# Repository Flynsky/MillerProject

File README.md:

This design is a TOP SECRET Miller Project.

Arbeits Aufteilung:
-  Ibex-Port (Handl)
- PCB, Schematic + Layout (Gewiese)
- USB PHY, ISO7816 Interface / Card VCC-Switching, Power Domains (Belm)
- Pin Assignment, Constraints, Bringup-Testinfrastruktur - Bindeglied zwischen Hardware und HDL (Drüen)

ToDo Redesign:
- USB-Phy reindesignen (voraussichtlich TUSB1106)
- zusätzlicher USB-Connector für Device-Mode-USB und Routing zum
TUSB1106. Also Referenzimplementierung kann hier das Sonata-Board
(lowRISC) dienen
- ISO7816-Interface: Das sind nur FPGA-Pins die an PIN-Header geroutet
werden. Ggf. noch Level-Shifter
- Alles raus was wir nicht brauchen
- Bissl hübscher machen

References
- [colone chips gatemate](https://colognechip.com/programmable-logic/gatemate/)
- [reference board GateMateA1-EVB](https://github.com/OLIMEX/GateMateA1-EVB)

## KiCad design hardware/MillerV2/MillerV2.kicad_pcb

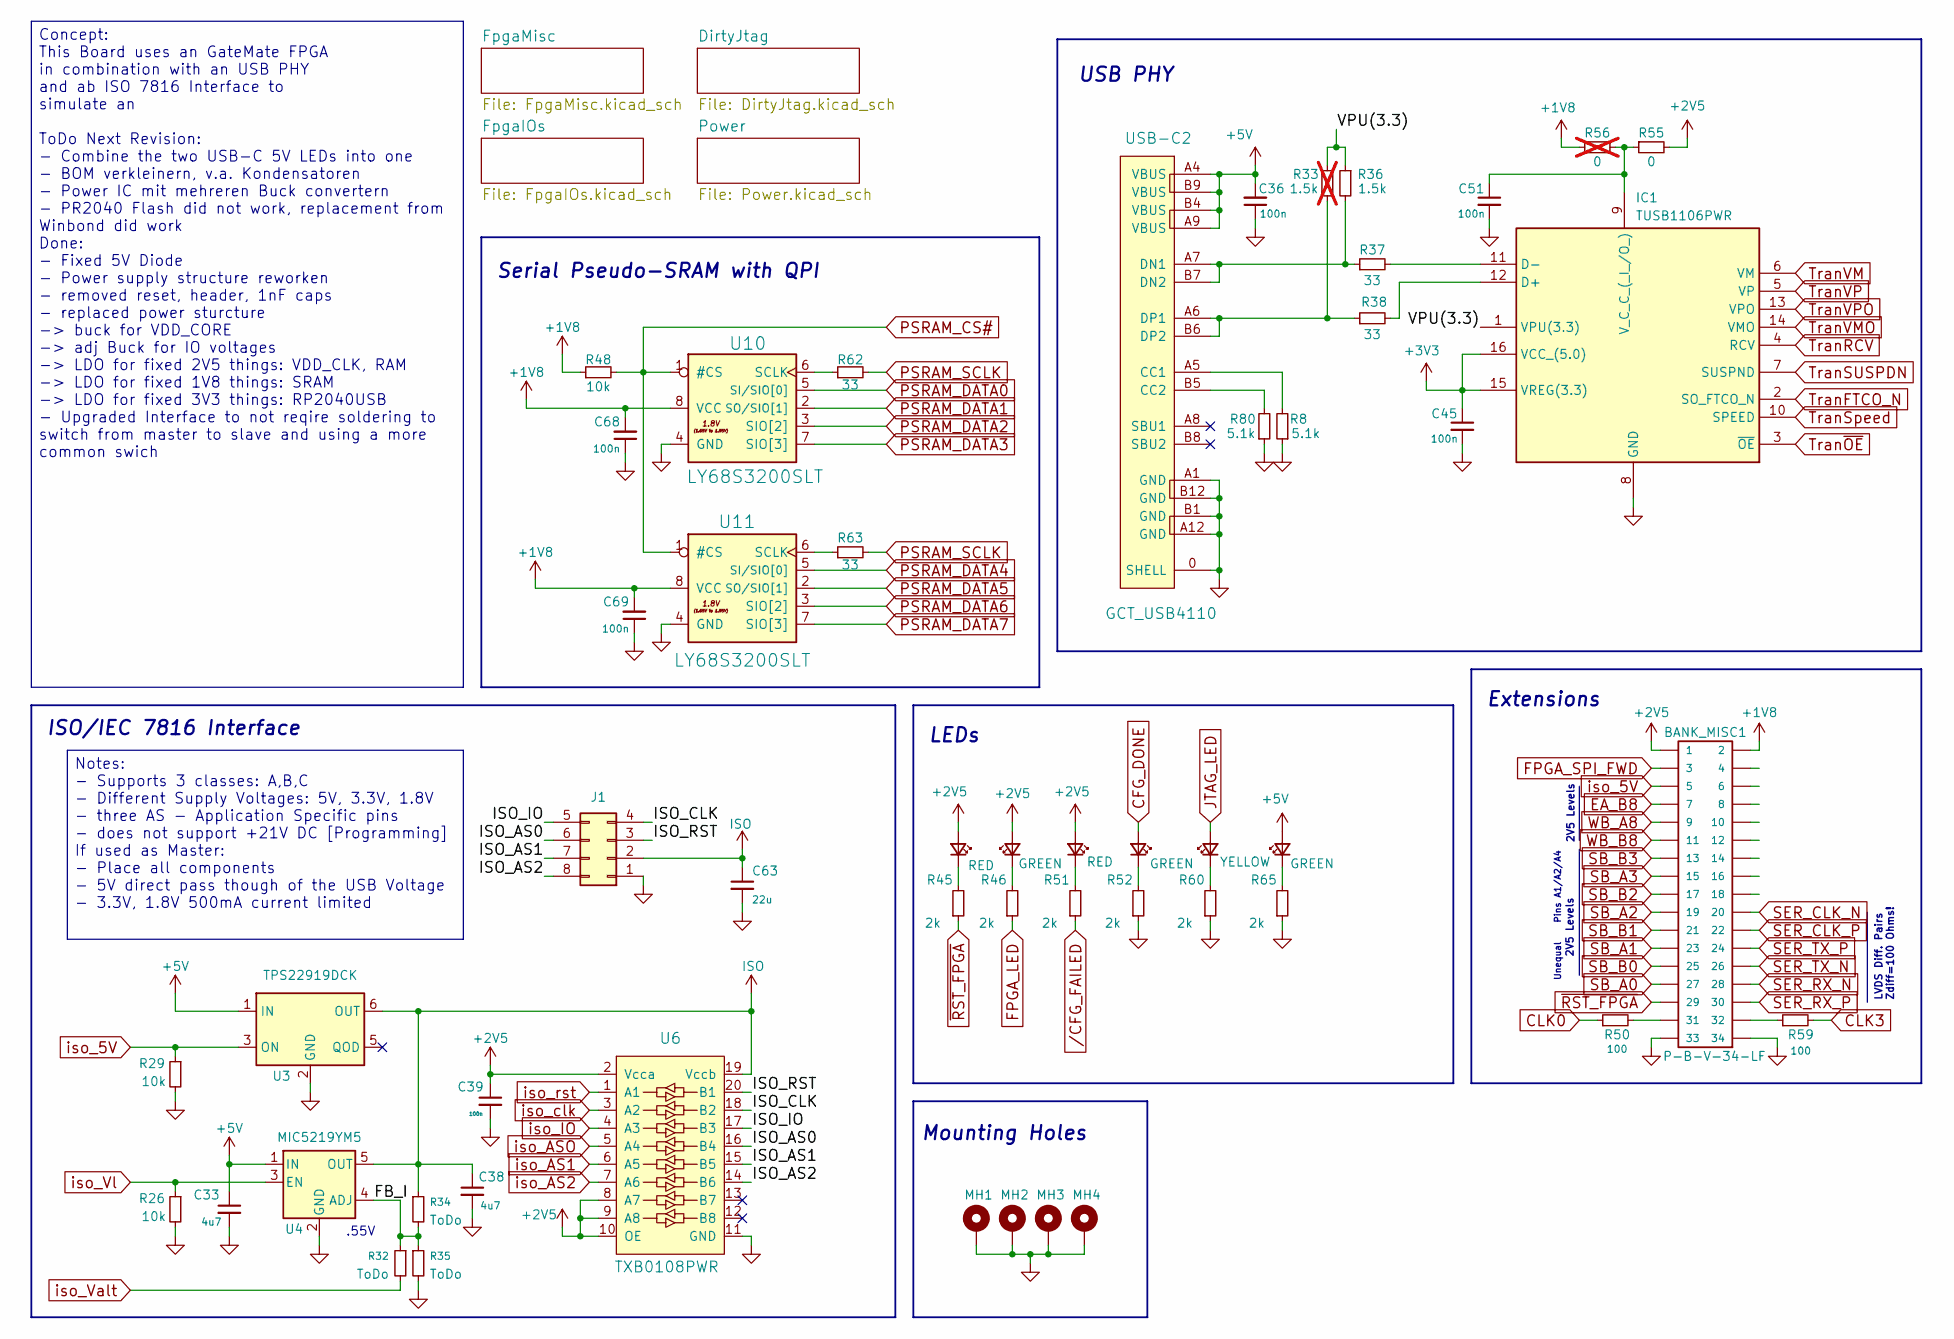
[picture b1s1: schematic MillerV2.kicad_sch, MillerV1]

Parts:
BANK_MISC1: P-B-V-34-LF; PinSocket_2x17_P2.54mm_Vertical_SMD
C33, C38: 4u7; C_0402_1005Metric
C36, C39, C45, C51, C68, C69: 100n; C_0402_1005Metric
C63: 22u; C_0805_2012Metric
CFG_DONE1: GREEN; LED_0402_1005Metric
CFG_FAIL1: RED; LED_0402_1005Metric
FPGA_LED1: GREEN; LED_0402_1005Metric
FPGA_RST2: RED; LED_0402_1005Metric
IC1: TUSB1106PWR; SOP65P640X120-16N; Mouser Part Number 595-TUSB1106PWR
J1: Conn_02x04_Counter_Clockwise; PinHeader_2x04_P2.54mm_Horizontal
JTAG_LED1: YELLOW; LED_0402_1005Metric
MH1, MH2, MH3, MH4: MountingHole_Pad; MountingHole_3.2mm_M3_Pad_Via
PWR_LED1: GREEN; LED_0402_1005Metric
R8, R80: 5.1k; R_0402_1005Metric
R26, R29, R48: 10k; R_0402_1005Metric
R32, R34, R35: ToDo; R_0402_1005Metric
R33: 1.5k; R_0402_1005Metric; not fitted
R36: 1.5k; R_0402_1005Metric
R37, R38, R62, R63: 33; R_0402_1005Metric
R45, R46, R51, R52, R60, R65: 2k; R_0402_1005Metric
R50, R59: 100; R_0402_1005Metric
R55: 0; R_0402_1005Metric
R56: 0; R_0402_1005Metric; not fitted
U3: TPS22919DCK; SOT-363_SC-70-6
U4: MIC5219YM5; SOT-23-5
U6: TXB0108PWR; TSSOP20_Pitch-0.65mm_6.6x4.5x1.2mm
U10, U11: LY68S3200SLT; SOIC-8_3.9x4.9mm_P1.27mm
USB-C2: GCT_USB4110; USB421603A

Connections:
+1V8: BANK_MISC1.2, C68.2, C69.2, R48.1, R56.1, U10.8 (VCC), U11.8 (VCC); also elsewhere on the board
+2V5: BANK_MISC1.1, C39.1, CFG_FAIL1.2 (A), FPGA_LED1.2 (A), FPGA_RST2.2 (A), R55.2, U6.2 (Vcca), U6.8 (A7), U6.9 (A8), U6.10 (OE); also elsewhere on the board
+3V3: C45.1, IC1.15 (VREG(3.3)), IC1.16 (VCC_(5.0)); also elsewhere on the board
+5V: C33.1, C36.2, PWR_LED1.2 (A), U3.1 (IN), U4.1 (IN), USB-C2.A4 (VBUS), USB-C2.A9 (VBUS), USB-C2.B4 (VBUS), USB-C2.B9 (VBUS); also elsewhere on the board
/FB_I: R32.1, R34.2, R35.1, U4.4 (ADJ)
/ISO_AS0: J1.6, U6.16 (B4)
/ISO_AS1: J1.7, U6.15 (B5)
/ISO_AS2: J1.8, U6.14 (B6)
/ISO_CLK: J1.4, U6.18 (B2)
/ISO_IO: J1.5, U6.17 (B3)
/ISO_RST: J1.3, U6.20 (B1)
/VPU(3.3): IC1.1 (VPU(3.3)), R33.1, R36.1
CFG_DONE: CFG_DONE1.2 (A); also elsewhere on the board
CLK0: R50.1; also elsewhere on the board
CLK3: R59.2; also elsewhere on the board
EA_B8: BANK_MISC1.7; also elsewhere on the board
FPGA_LED: R46.1; also elsewhere on the board
FPGA_SPI_FWD: BANK_MISC1.3; also elsewhere on the board
GND: BANK_MISC1.33, BANK_MISC1.34, C33.2, C36.1, C38.2, C39.2, C45.2, C51.2, C63.2, C68.1, C69.1, IC1.8 (GND), J1.1, MH1.1 (1_1), MH2.1 (1_1), MH3.1 (1_1), MH4.1 (1_1), R8.1, R26.2, R29.2, R35.2, R52.1, R60.1, R65.1, R80.1, U3.2 (GND), U4.2 (GND), U6.11 (GND), U10.4 (GND), U11.4 (GND), USB-C2.0 (SHELL), USB-C2.A1 (GND), USB-C2.A12 (GND), USB-C2.B1 (GND), USB-C2.B12 (GND); also elsewhere on the board
ISO: C38.1, C63.1, J1.2, R34.1, U3.6 (OUT), U4.5 (OUT), U6.19 (Vccb)
JTAG_LED: JTAG_LED1.2 (A); also elsewhere on the board
unnamed: BANK_MISC1.31, R50.2
unnamed: BANK_MISC1.32, R59.1
unnamed: CFG_DONE1.1 (K), R52.2
unnamed: CFG_FAIL1.1 (K), R51.2
unnamed: FPGA_LED1.1 (K), R46.2
unnamed: FPGA_RST2.1 (K), R45.2
unnamed: IC1.12 (D+), R38.2
unnamed: IC1.11 (D-), R37.2
unnamed: C51.1, IC1.9 (V_C_C_(_I_/O_)), R55.1, R56.2
unnamed: JTAG_LED1.1 (K), R60.2
unnamed: PWR_LED1.1 (K), R65.2
unnamed: R62.1, U10.6 (SCLK)
unnamed: R63.1, U11.6 (SCLK)
unnamed: R8.2, USB-C2.A5 (CC1)
unnamed: R80.2, USB-C2.B5 (CC2)
unnamed: R36.2, R37.1, USB-C2.A7 (DN1), USB-C2.B7 (DN2)
unnamed: R33.2, R38.1, USB-C2.A6 (DP1), USB-C2.B6 (DP2)
PSRAM_CS#: R48.2, U10.1 (#CS), U11.1 (#CS); also elsewhere on the board
PSRAM_DATA0: U10.5 (SI/SIO[0]); also elsewhere on the board
PSRAM_DATA1: U10.2 (SO/SIO[1]); also elsewhere on the board
PSRAM_DATA2: U10.3 (SIO[2]); also elsewhere on the board
PSRAM_DATA3: U10.7 (SIO[3]); also elsewhere on the board
PSRAM_DATA4: U11.5 (SI/SIO[0]); also elsewhere on the board
PSRAM_DATA5: U11.2 (SO/SIO[1]); also elsewhere on the board
PSRAM_DATA6: U11.3 (SIO[2]); also elsewhere on the board
PSRAM_DATA7: U11.7 (SIO[3]); also elsewhere on the board
PSRAM_SCLK: R62.2, R63.2; also elsewhere on the board
SB_A0: BANK_MISC1.27
SB_A1: BANK_MISC1.23
SB_A2: BANK_MISC1.19
SB_A3: BANK_MISC1.15
SB_B0: BANK_MISC1.25
SB_B1: BANK_MISC1.21
SB_B2: BANK_MISC1.17
SB_B3: BANK_MISC1.13
SER_CLK_N: BANK_MISC1.20; also elsewhere on the board
SER_CLK_P: BANK_MISC1.22; also elsewhere on the board
SER_RX_N: BANK_MISC1.28; also elsewhere on the board
SER_RX_P: BANK_MISC1.30; also elsewhere on the board
SER_TX_N: BANK_MISC1.26; also elsewhere on the board
SER_TX_P: BANK_MISC1.24; also elsewhere on the board
TranFTCO_N: IC1.2 (SO_FTCO_N); also elsewhere on the board
TranRCV: IC1.4 (RCV); also elsewhere on the board
TranSUSPDN: IC1.7 (SUSPND); also elsewhere on the board
TranSpeed: IC1.10 (SPEED); also elsewhere on the board
TranVM: IC1.6 (VM); also elsewhere on the board
TranVMO: IC1.14 (VMO); also elsewhere on the board
TranVP: IC1.5 (VP); also elsewhere on the board
TranVPO: IC1.13 (VPO); also elsewhere on the board
Tran~OE: IC1.3 (~OE); also elsewhere on the board
WB_A8: BANK_MISC1.9; also elsewhere on the board
WB_B8: BANK_MISC1.11; also elsewhere on the board
iso_5V: BANK_MISC1.5, R29.1, U3.3 (ON); also elsewhere on the board
iso_AS1: U6.6 (A5); also elsewhere on the board
iso_AS2: U6.7 (A6); also elsewhere on the board
iso_ASO: U6.5 (A4); also elsewhere on the board
iso_IO: U6.4 (A3); also elsewhere on the board
iso_Valt: R32.2; also elsewhere on the board
iso_Vl: R26.1, U4.3 (EN); also elsewhere on the board
iso_clk: U6.3 (A2); also elsewhere on the board
iso_rst: U6.1 (A1); also elsewhere on the board
/CFG_FAILED: R51.1; also elsewhere on the board
~RST_FPGA: BANK_MISC1.29, R45.1; also elsewhere on the board

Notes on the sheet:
.55V
Unequal Pins A1/A2/A4
2V5 Levels
ISO/IEC 7816 Interface
LEDs
Serial Pseudo-SRAM with QPI
Extensions
USB PHY
LVDS Diff. Pairs Zdiff=100 Ohms!
Mounting Holes
Concept: This Board uses an GateMate FPGA in combination with an USB PHY and ab ISO 7816 Interface to simulate an ToDo Next Revision: - Combine the two USB-C 5V LEDs into one - BOM verkleinern, v.a. Kondensatoren - Power IC mit mehreren Buck convertern - PR2040 Flash did not work, replacement from 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
Notes: - Supports 3 classes: A,B,C - Different Supply Voltages: 5V, 3.3V, 1.8V - three AS - Application Specific pins - does not support +21V DC [Programming] If used as Master: - Place all components - 5V direct pass though of the USB Voltage - 3.3V, 1.8V 500mA current limited

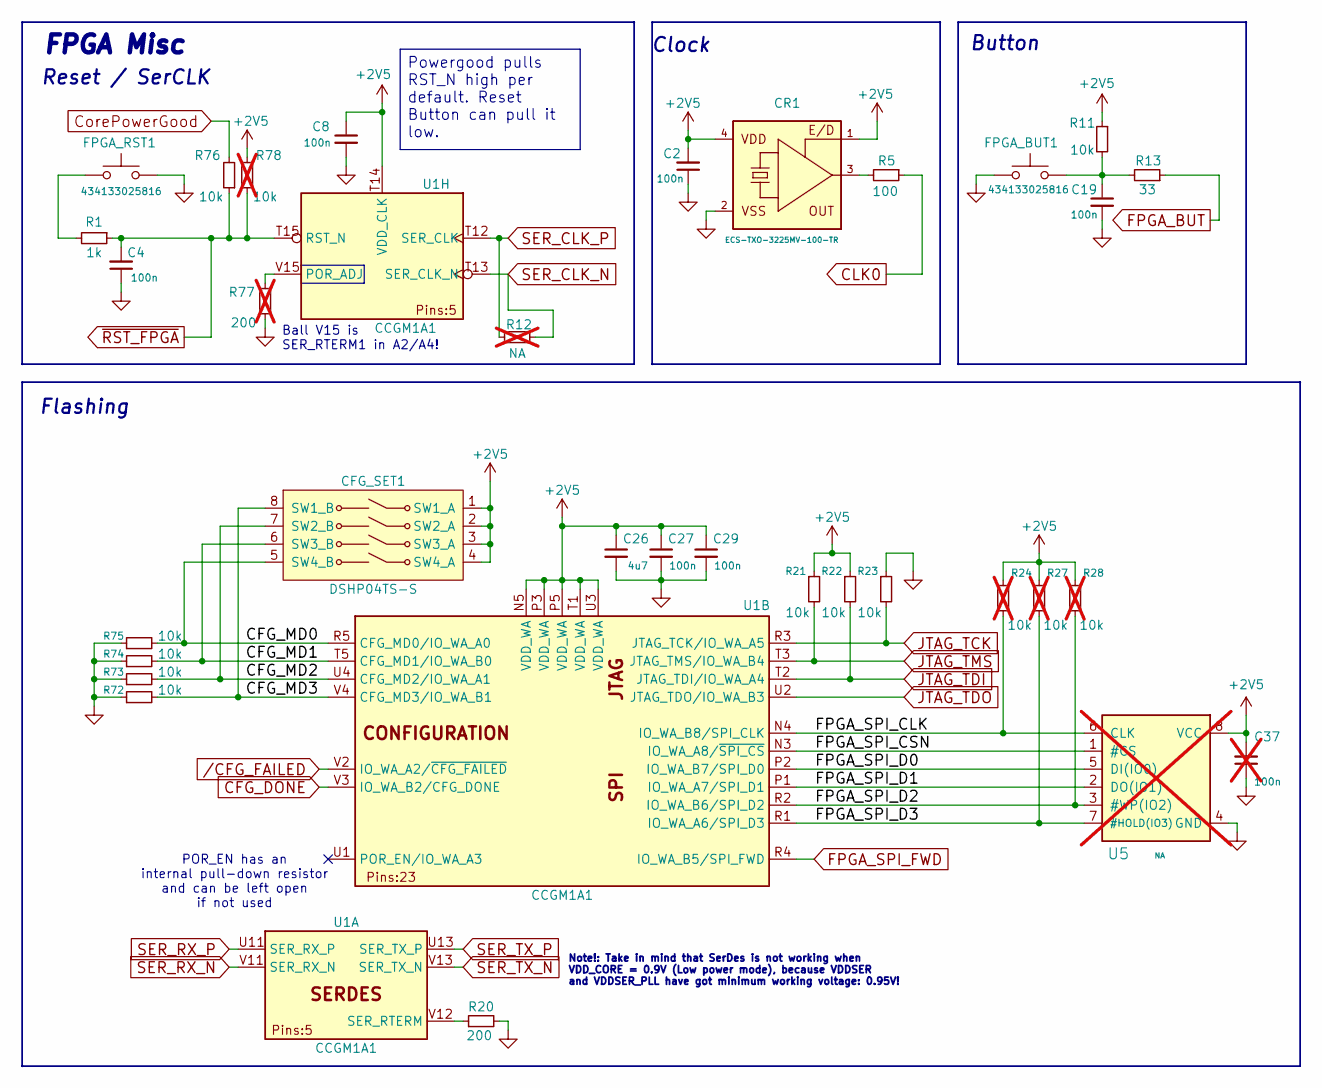
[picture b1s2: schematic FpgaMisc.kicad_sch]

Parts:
C2, C4, C8, C19, C27, C29: 100n; C_0402_1005Metric
C26: 4u7; C_0402_1005Metric
C37: 100n; C_0402_1005Metric; not fitted
CFG_SET1: DSHP04TS-S; SW_DIP_SPSTx04_Slide_KingTek_DSHP04TS_W7.62mm_P1.27mm
CR1: ECS-TXO-3225MV-100-TR; Oscillator_SMD_Abracon_ASE-4Pin_3.2x2.5mm_HandSoldering
FPGA_BUT1: 434133025816; SW_Push_1P1T_NO_Vertical_Wuerth_434133025816
FPGA_RST1: 434133025816; SW_Push_1P1T_NO_Vertical_Wuerth_434133025816
R1: 1k; R_0402_1005Metric
R5: 100; R_0402_1005Metric
R11, R21, R22, R23, R72, R73, R74, R75, R76: 10k; R_0402_1005Metric
R12: NA; R_0402_1005Metric; not fitted
R13: 33; R_0402_1005Metric
R20: 200; R_0402_1005Metric
R24, R27, R28, R78: 10k; R_0402_1005Metric; not fitted
R77: 200; R_0402_1005Metric; not fitted
U1: CCGM1A1; BGA-324_15x15mm_Layout18x18_P0.8mm_improvedUrsprung
U5: NA; SOIC-8_5.3x5.3mm_P1.27mm; not fitted

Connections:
+2V5: C2.2, C8.1, C26.1, C27.1, C29.1, C37.2, CFG_SET1.1 (SW1_A), CFG_SET1.2 (SW2_A), CFG_SET1.3 (SW3_A), CFG_SET1.4 (SW4_A), CR1.1 (E/D), CR1.4 (VDD), R11.1, R21.1, R22.1, R24.1, R27.1, R28.1, R78.2, U1.N5 (VDD_WA), U1.P3 (VDD_WA), U1.P5 (VDD_WA), U1.T1 (VDD_WA), U1.T14 (VDD_CLK), U1.U3 (VDD_WA), U5.8 (VCC); also elsewhere on the board
/FpgaMisc/CFG_MD0: CFG_SET1.5 (SW4_B), R75.2, U1.R5 (CFG_MD0/IO_WA_A0)
/FpgaMisc/CFG_MD1: CFG_SET1.6 (SW3_B), R74.2, U1.T5 (CFG_MD1/IO_WA_B0)
/FpgaMisc/CFG_MD2: CFG_SET1.7 (SW2_B), R73.2, U1.U4 (CFG_MD2/IO_WA_A1)
/FpgaMisc/CFG_MD3: CFG_SET1.8 (SW1_B), R72.2, U1.V4 (CFG_MD3/IO_WA_B1)
/FpgaMisc/FPGA_SPI_CLK: R24.2, U1.N4 (IO_WA_B8/SPI_CLK), U5.6 (CLK)
/FpgaMisc/FPGA_SPI_CSN: U1.N3 (IO_WA_A8/~SPI_CS), U5.1 (#CS)
/FpgaMisc/FPGA_SPI_D0: U1.P2 (IO_WA_B7/SPI_D0), U5.5 (DI(IO0))
/FpgaMisc/FPGA_SPI_D1: U1.P1 (IO_WA_A7/SPI_D1), U5.2 (DO(IO1))
/FpgaMisc/FPGA_SPI_D2: R28.2, U1.R2 (IO_WA_B6/SPI_D2), U5.3 (#WP(IO2))
/FpgaMisc/FPGA_SPI_D3: R27.2, U1.R1 (IO_WA_A6/SPI_D3), U5.7 (#HOLD(IO3))
CFG_DONE: U1.V3 (IO_WA_B2/CFG_DONE); also elsewhere on the board
CLK0: R5.1; also elsewhere on the board
CorePowerGood: R76.2; also elsewhere on the board
FPGA_BUT: R13.1; also elsewhere on the board
FPGA_SPI_FWD: U1.R4 (IO_WA_B5/SPI_FWD); also elsewhere on the board
GND: C2.1, C4.1, C8.2, C19.2, C26.2, C27.2, C29.2, C37.1, CR1.2 (VSS), FPGA_BUT1.1, FPGA_RST1.2, R20.2, R23.1, R72.1, R73.1, R74.1, R75.1, R77.1, U5.4 (GND); also elsewhere on the board
JTAG_TCK: R23.2, U1.R3 (JTAG_TCK/IO_WA_A5); also elsewhere on the board
JTAG_TDI: R22.2, U1.T2 (JTAG_TDI/IO_WA_A4); also elsewhere on the board
JTAG_TDO: U1.U2 (JTAG_TDO/IO_WA_B3); also elsewhere on the board
JTAG_TMS: R21.2, U1.T3 (JTAG_TMS/IO_WA_B4); also elsewhere on the board
unnamed: C19.1, FPGA_BUT1.2, R11.2, R13.2
unnamed: CR1.3 (OUT), R5.2
unnamed: FPGA_RST1.1, R1.2
unnamed: R20.1, U1.V12 (SER_RTERM)
unnamed: R77.2, U1.V15 (POR_ADJ)
SER_CLK_N: R12.2, U1.T13 (SER_CLK_N); also elsewhere on the board
SER_CLK_P: R12.1, U1.T12 (SER_CLK); also elsewhere on the board
SER_RX_N: U1.V11 (SER_RX_N); also elsewhere on the board
SER_RX_P: U1.U11 (SER_RX_P); also elsewhere on the board
SER_TX_N: U1.V13 (SER_TX_N); also elsewhere on the board
SER_TX_P: U1.U13 (SER_TX_P); also elsewhere on the board
/CFG_FAILED: U1.V2 (IO_WA_A2/~CFG_FAILED); also elsewhere on the board
~RST_FPGA: C4.2, R1.1, R76.1, R78.1, U1.T15 (RST_N); also elsewhere on the board

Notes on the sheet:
Note!: Take in mind that SerDes is not working when VDD_CORE = 0.9V (Low power mode), because VDDSER and VDDSER_PLL have got minimum working voltage: 0.95V!
FPGA Misc
Flashing
Ball V15 is SER_RTERM1 in A2/A4!
POR_EN has an internal pull-down resistor and can be left open if not used
Clock
Button
Reset / SerCLK
Powergood pulls RST_N high per default. Reset Button can pull it low.

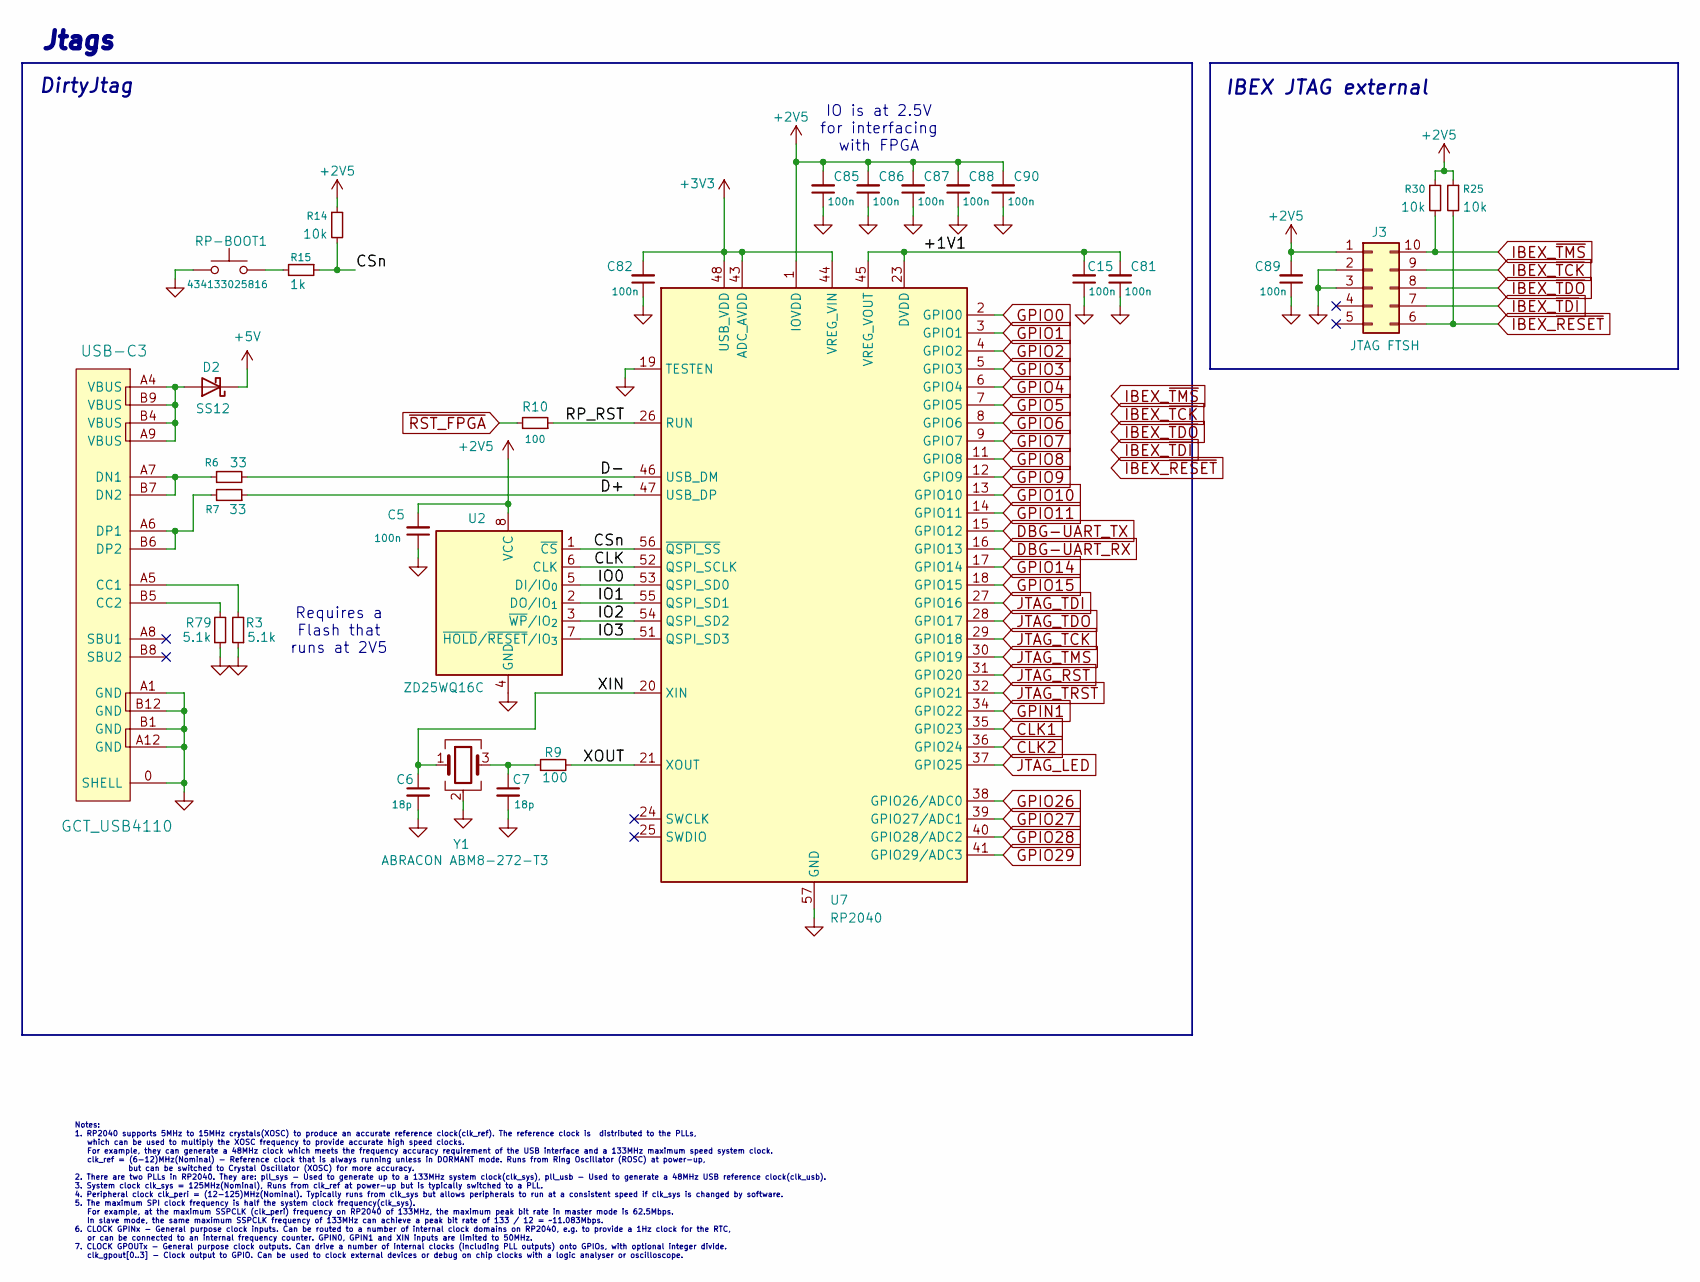
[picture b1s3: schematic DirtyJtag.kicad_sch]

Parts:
C5, C15, C81, C82, C85, C86, C87, C88, C89, C90: 100n; C_0402_1005Metric
C6, C7: 18p; C_0402_1005Metric
D2: SS12; D_SOD-123; LCSC C84354
J3: JTAG FTSH; FTSH10501LDVK
R3, R79: 5.1k; R_0402_1005Metric
R6, R7: 33; R_0402_1005Metric
R9, R10: 100; R_0402_1005Metric
R14, R25, R30: 10k; R_0402_1005Metric
R15: 1k; R_0402_1005Metric
RP-BOOT1: 434133025816; SW_Push_1P1T_NO_Vertical_Wuerth_434133025816
U2: ZD25WQ16C; SOIC-8_5.3x5.3mm_P1.27mm
U7: RP2040; QFN-56-1EP_7x7mm_P0.4mm_EP3.2x3.2mm
USB-C3: GCT_USB4110; USB421603A
Y1: ABRACON ABM8-272-T3; Oscillator_SMD_Abracon_ASE-4Pin_3.2x2.5mm_HandSoldering

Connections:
+2V5: C5.2, C85.2, C86.2, C87.2, C88.2, C89.2, C90.2, J3.1, R14.1, R25.1, R30.1, U2.8 (VCC), U7.1 (IOVDD), U7.10 (IOVDD), U7.22 (IOVDD), U7.33 (IOVDD), U7.42 (IOVDD), U7.49 (IOVDD); also elsewhere on the board
+3V3: C82.2, U7.43 (ADC_AVDD), U7.44 (VREG_VIN), U7.48 (USB_VDD); also elsewhere on the board
+5V: D2.1 (K); also elsewhere on the board
/DirtyJtag/+1V1: C15.2, C81.2, U7.23 (DVDD), U7.45 (VREG_VOUT), U7.50 (DVDD)
/DirtyJtag/CLK: U2.6 (CLK), U7.52 (QSPI_SCLK)
/DirtyJtag/CSn: R14.2, R15.1, U2.1 (~CS), U7.56 (~QSPI_SS)
/DirtyJtag/D+: R7.1, U7.47 (USB_DP)
/DirtyJtag/D-: R6.2, U7.46 (USB_DM)
/DirtyJtag/IO0: U2.5 (DI/IO_{0}), U7.53 (QSPI_SD0)
/DirtyJtag/IO1: U2.2 (DO/IO_{1}), U7.55 (QSPI_SD1)
/DirtyJtag/IO2: U2.3 (~WP/IO_{2}), U7.54 (QSPI_SD2)
/DirtyJtag/IO3: U2.7 (~HOLD/~RESET/IO_{3}), U7.51 (QSPI_SD3)
/DirtyJtag/RP_RST: R10.1, U7.26 (RUN)
/DirtyJtag/XIN: C6.1, U7.20 (XIN), Y1.1
/DirtyJtag/XOUT: R9.2, U7.21 (XOUT)
CLK1: U7.35 (GPIO23); also elsewhere on the board
CLK2: U7.36 (GPIO24); also elsewhere on the board
DBG-UART_RX: U7.16 (GPIO13); also elsewhere on the board
DBG-UART_TX: U7.15 (GPIO12); also elsewhere on the board
GND: C5.1, C6.2, C7.2, C15.1, C81.1, C82.1, C85.1, C86.1, C87.1, C88.1, C89.1, C90.1, J3.2, J3.3, R3.1, R79.1, RP-BOOT1.1, U2.4 (GND), U7.19 (TESTEN), U7.57 (GND), USB-C3.0 (SHELL), USB-C3.A1 (GND), USB-C3.A12 (GND), USB-C3.B1 (GND), USB-C3.B12 (GND), Y1.2 (G), Y1.4 (G); also elsewhere on the board
GPIN1: U7.34 (GPIO22); also elsewhere on the board
GPIO0: U7.2 (GPIO0); also elsewhere on the board
GPIO1: U7.3 (GPIO1); also elsewhere on the board
GPIO2: U7.4 (GPIO2); also elsewhere on the board
GPIO3: U7.5 (GPIO3); also elsewhere on the board
GPIO4: U7.6 (GPIO4); also elsewhere on the board
GPIO5: U7.7 (GPIO5); also elsewhere on the board
GPIO6: U7.8 (GPIO6); also elsewhere on the board
GPIO7: U7.9 (GPIO7); also elsewhere on the board
GPIO8: U7.11 (GPIO8); also elsewhere on the board
GPIO9: U7.12 (GPIO9); also elsewhere on the board
GPIO10: U7.13 (GPIO10); also elsewhere on the board
GPIO11: U7.14 (GPIO11); also elsewhere on the board
GPIO14: U7.17 (GPIO14); also elsewhere on the board
GPIO15: U7.18 (GPIO15); also elsewhere on the board
GPIO26: U7.38 (GPIO26/ADC0); also elsewhere on the board
GPIO27: U7.39 (GPIO27/ADC1); also elsewhere on the board
GPIO28: U7.40 (GPIO28/ADC2); also elsewhere on the board
GPIO29: U7.41 (GPIO29/ADC3); also elsewhere on the board
IBEX_~RESET: J3.6, R25.2
IBEX_~TCK: J3.9
IBEX_~TDI: J3.7
IBEX_~TDO: J3.8
IBEX_~TMS: J3.10, R30.2
JTAG_LED: U7.37 (GPIO25); also elsewhere on the board
JTAG_RST: U7.31 (GPIO20)
JTAG_TCK: U7.29 (GPIO18); also elsewhere on the board
JTAG_TDI: U7.27 (GPIO16); also elsewhere on the board
JTAG_TDO: U7.28 (GPIO17); also elsewhere on the board
JTAG_TMS: U7.30 (GPIO19); also elsewhere on the board
JTAG_TRST: U7.32 (GPIO21)
unnamed: C7.1, R9.1, Y1.3
unnamed: D2.2 (A), USB-C3.A4 (VBUS), USB-C3.A9 (VBUS), USB-C3.B4 (VBUS), USB-C3.B9 (VBUS)
unnamed: R15.2, RP-BOOT1.2
unnamed: R3.2, USB-C3.A5 (CC1)
unnamed: R79.2, USB-C3.B5 (CC2)
unnamed: R6.1, USB-C3.A7 (DN1), USB-C3.B7 (DN2)
unnamed: R7.2, USB-C3.A6 (DP1), USB-C3.B6 (DP2)
~RST_FPGA: R10.2; also elsewhere on the board

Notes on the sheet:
IO is at 2.5V for interfacing with FPGA
Jtags
DirtyJtag
Notes: 1. RP2040 supports 5MHz to 15MHz crystals(XOSC) to produce an accurate reference clock(clk_ref). The reference clock is distributed to the PLLs, which can be used to multiply the XOSC frequency to provide accurate high speed clocks. For example, they can generate a 48MHz clock which meets th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
IBEX JTAG external
Requires a Flash that runs at 2V5

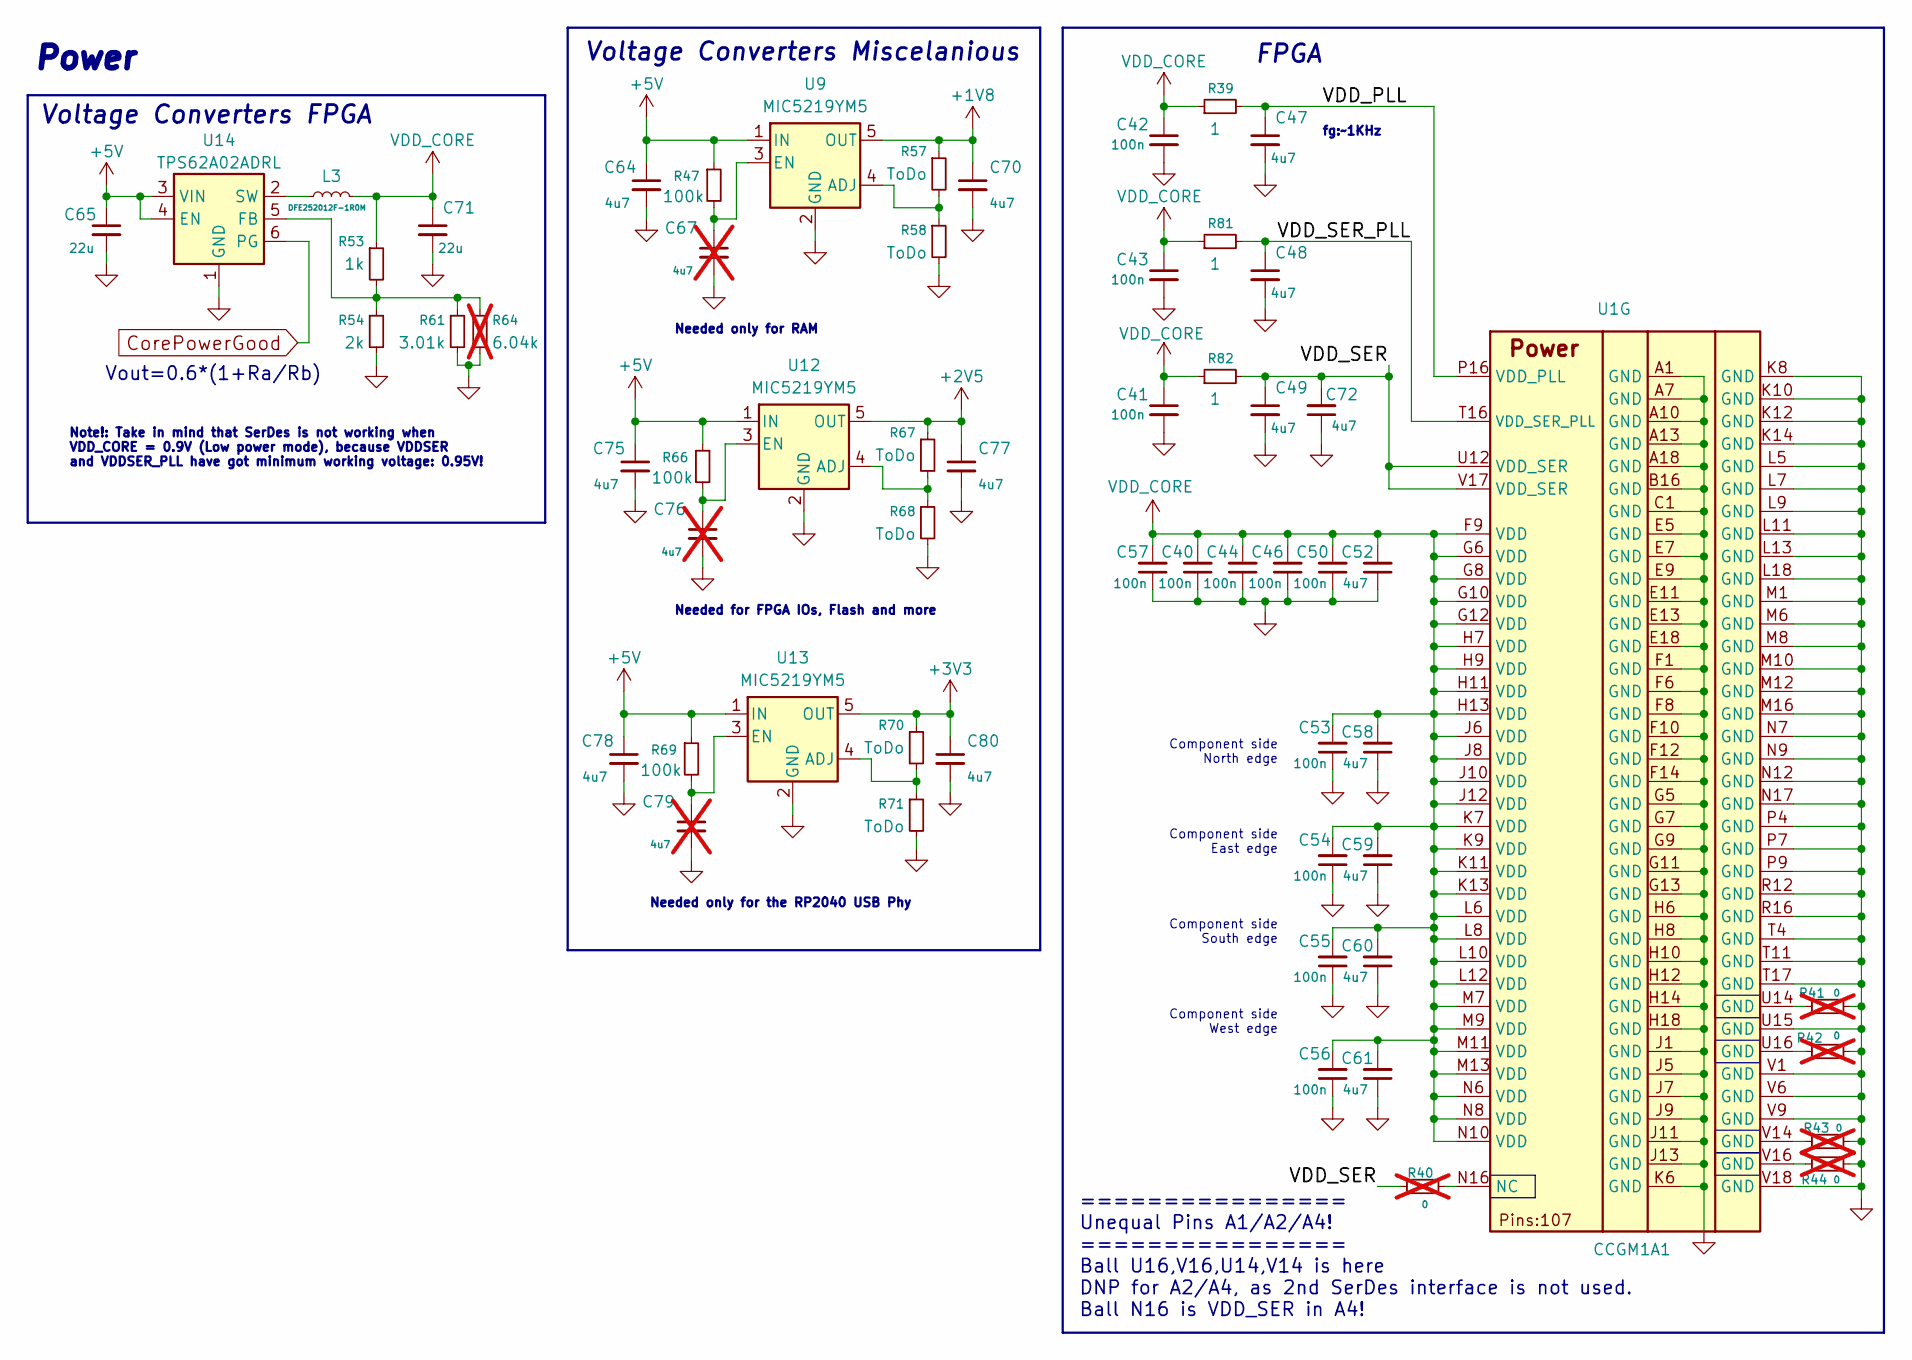
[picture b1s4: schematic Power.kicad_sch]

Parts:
C40, C41, C42, C43, C44, C46, C50, C53, C54, C55, C56, C57: 100n; C_0402_1005Metric
C47, C48, C49, C52, C58, C59, C60, C61, C64, C70, C72, C75, C77, C78, C80: 4u7; C_0402_1005Metric
C65, C71: 22u; C_0805_2012Metric
C67, C76, C79: 4u7; C_0402_1005Metric; not fitted
L3: DFE252012F-1R0M; L_1008_2520Metric
R39, R81, R82: 1; R_0402_1005Metric
R40, R41, R42, R43, R44: 0; R_0402_1005Metric; not fitted
R47, R66, R69: 100k; R_0402_1005Metric
R53: 1k; R_0402_1005Metric
R54: 2k; R_0402_1005Metric
R57, R58, R67, R68, R70, R71: ToDo; R_0402_1005Metric
R61: 3.01k; R_0402_1005Metric
R64: 6.04k; R_0402_1005Metric; not fitted
U1: CCGM1A1; BGA-324_15x15mm_Layout18x18_P0.8mm_improvedUrsprung
U9, U12, U13: MIC5219YM5; SOT-23-5
U14: TPS62A02ADRL; SOT-563

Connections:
+1V8: C70.1, R57.1, U9.5 (OUT); also elsewhere on the board
+2V5: C77.1, R67.1, U12.5 (OUT); also elsewhere on the board
+3V3: C80.1, R70.1, U13.5 (OUT); also elsewhere on the board
+5V: C64.1, C65.1, C75.1, C78.1, R47.1, R66.1, R69.1, U9.1 (IN), U12.1 (IN), U13.1 (IN), U14.3 (VIN), U14.4 (EN); also elsewhere on the board
/Power/VDD_PLL: C47.1, R39.2, U1.P16 (VDD_PLL)
/Power/VDD_SER: C49.1, C72.2, R40.1, R82.2, U1.U12 (VDD_SER), U1.V17 (VDD_SER)
/Power/VDD_SER_PLL: C48.1, R81.2, U1.T16 (VDD_SER_PLL)
CorePowerGood: U14.6 (PG); also elsewhere on the board
GND: C40.1, C41.2, C42.2, C43.2, C44.1, C46.1, C47.2, C48.2, C49.2, C50.1, C52.1, C53.1, C54.1, C55.1, C56.1, C57.1, C58.1, C59.1, C60.1, C61.1, C64.2, C65.2, C67.2, C70.2, C71.2, C72.1, C75.2, C76.2, C77.2, C78.2, C79.2, C80.2, R41.1, R42.1, R43.1, R44.1, R54.2, R58.2, R61.2, R64.2, R68.2, R71.2, U1.A1 (GND), U1.A7 (GND), U1.A10 (GND), U1.A13 (GND), U1.A18 (GND), U1.B16 (GND), U1.C1 (GND), U1.E5 (GND), U1.E7 (GND), U1.E9 (GND), U1.E11 (GND), U1.E13 (GND), U1.E18 (GND), U1.F1 (GND), U1.F6 (GND), U1.F8 (GND), U1.F10 (GND), U1.F12 (GND), U1.F14 (GND), U1.G5 (GND), U1.G7 (GND), U1.G9 (GND), U1.G11 (GND), U1.G13 (GND), U1.H6 (GND), U1.H8 (GND), U1.H10 (GND), U1.H12 (GND), U1.H14 (GND), U1.H18 (GND), U1.J1 (GND), U1.J5 (GND), U1.J7 (GND), U1.J9 (GND), U1.J11 (GND), U1.J13 (GND), U1.K6 (GND), U1.K8 (GND), U1.K10 (GND), U1.K12 (GND), U1.K14 (GND), U1.L5 (GND), U1.L7 (GND), U1.L9 (GND), U1.L11 (GND), U1.L13 (GND), U1.L18 (GND), U1.M1 (GND), U1.M6 (GND), U1.M8 (GND), U1.M10 (GND), U1.M12 (GND), U1.M16 (GND), U1.N7 (GND), U1.N9 (GND), U1.N12 (GND), U1.N17 (GND), U1.P4 (GND), U1.P7 (GND), U1.P9 (GND), U1.R12 (GND), U1.R16 (GND), U1.T4 (GND), U1.T11 (GND), U1.T17 (GND), U1.U15 (GND), U1.V1 (GND), U1.V6 (GND), U1.V9 (GND), U1.V18 (GND), U9.2 (GND), U12.2 (GND), U13.2 (GND), U14.1 (GND); also elsewhere on the board
unnamed: R41.2, U1.U14 (GND)
unnamed: R42.2, U1.U16 (GND)
unnamed: R43.2, U1.V14 (GND)
unnamed: R44.2, U1.V16 (GND)
unnamed: R40.2, U1.N16 (NC)
unnamed: R57.2, R58.1, U9.4 (ADJ)
unnamed: C67.1, R47.2, U9.3 (EN)
unnamed: R67.2, R68.1, U12.4 (ADJ)
unnamed: C76.1, R66.2, U12.3 (EN)
unnamed: R70.2, R71.1, U13.4 (ADJ)
unnamed: C79.1, R69.2, U13.3 (EN)
unnamed: R53.2, R54.1, R61.1, R64.1, U14.5 (FB)
unnamed: L3.1, U14.2 (SW)
VDD_CORE: C40.2, C41.1, C42.1, C43.1, C44.2, C46.2, C50.2, C52.2, C53.2, C54.2, C55.2, C56.2, C57.2, C58.2, C59.2, C60.2, C61.2, C71.1, L3.2, R39.1, R53.1, R81.1, R82.1, U1.F9 (VDD), U1.G6 (VDD), U1.G8 (VDD), U1.G10 (VDD), U1.G12 (VDD), U1.H7 (VDD), U1.H9 (VDD), U1.H11 (VDD), U1.H13 (VDD), U1.J6 (VDD), U1.J8 (VDD), U1.J10 (VDD), U1.J12 (VDD), U1.K7 (VDD), U1.K9 (VDD), U1.K11 (VDD), U1.K13 (VDD), U1.L6 (VDD), U1.L8 (VDD), U1.L10 (VDD), U1.L12 (VDD), U1.M7 (VDD), U1.M9 (VDD), U1.M11 (VDD), U1.M13 (VDD), U1.N6 (VDD), U1.N8 (VDD), U1.N10 (VDD)

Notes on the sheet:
Needed only for RAM
Note!: Take in mind that SerDes is not working when VDD_CORE = 0.9V (Low power mode), because VDDSER and VDDSER_PLL have got minimum working voltage: 0.95V!
Needed only for the RP2040 USB Phy
fg:~1KHz
Component side East edge
Component side West edge
Voltage Converters Miscelanious
Component side South edge
Vout=0.6*(1+Ra/Rb)
================ Unequal Pins A1/A2/A4! ================ Ball U16,V16,U14,V14 is here DNP for A2/A4, as 2nd SerDes interface is not used. Ball N16 is VDD_SER in A4!
Component side North edge
Needed for FPGA IOs, Flash and more
Voltage Converters FPGA
FPGA
Power
